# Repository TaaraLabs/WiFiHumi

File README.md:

Wifi Humidity Sensor
====================

[WebSite](https://taaralabs.eu/wh1)

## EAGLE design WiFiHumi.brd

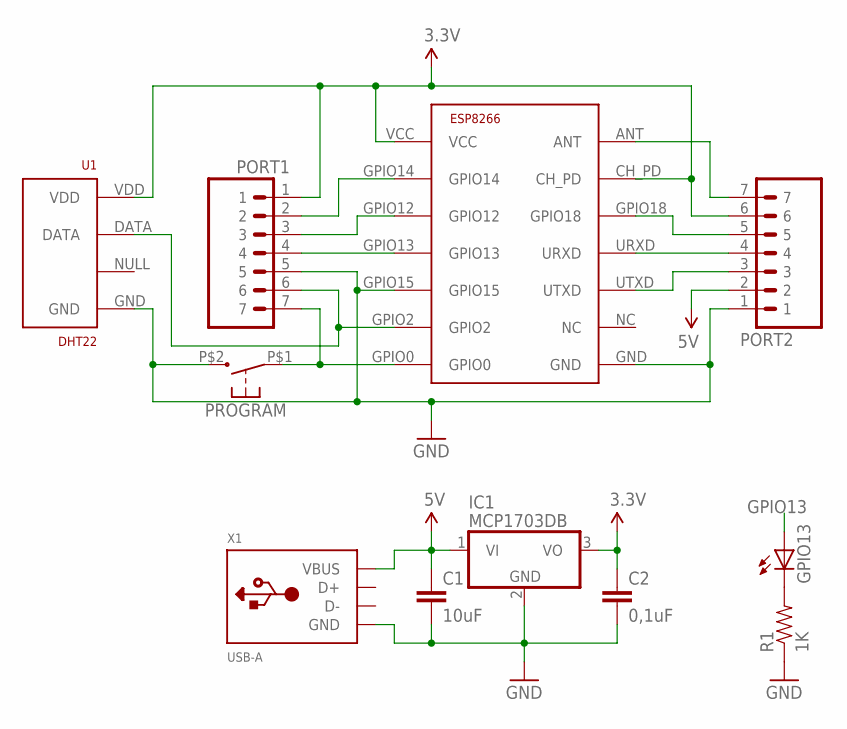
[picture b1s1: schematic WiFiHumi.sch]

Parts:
C1: 10uF; 0603-CAP
C2: 0,1uF; 0603-CAP
GPIO13: LEDCHIPLED_0603; CHIPLED_0603
IC1: MCP1703DB; SOT223
PORT1, PORT2: DIPLOCK7-FEMALE; 1X07_FEMALE_LOCK.010
PROGRAM: OMRON_B3U-1000_TACT_SW; BC3-1000
R1: 1K; 0603-RES
U1: DHT22; RHT03_DHT-22/RA
U$1: ESP8266; ESP-03
X1: USB-A; MOLEX_480371000

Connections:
3.3V: C2.1, IC1.3 (VO), PORT1.1, PORT2.6, U1.VDD, U$1.CH_PD, U$1.VCC
5V: C1.1, IC1.1 (VI), PORT2.2, X1.1 (VBUS)
ANT: PORT2.7, U$1.ANT
GND: C1.2, C2.2, IC1.2 (GND), PORT1.5, PORT2.1, PROGRAM.P$2 (3), R1.1, U1.GND, U$1.GND, U$1.GPIO15, X1.4 (GND)
GPIO0: PORT1.7, PROGRAM.P$1 (1), U$1.GPIO0
GPIO02: PORT1.6, U1.DATA, U$1.GPIO2
GPIO12: PORT1.3, U$1.GPIO12
GPIO13: GPIO13.A, PORT1.4, U$1.GPIO13
GPIO14: PORT1.2, U$1.GPIO14
GPIO18: PORT2.5, U$1.GPIO18
unnamed: GPIO13.C, R1.2
RXD: PORT2.4, U$1.URXD
TXD: PORT2.3, U$1.UTXD

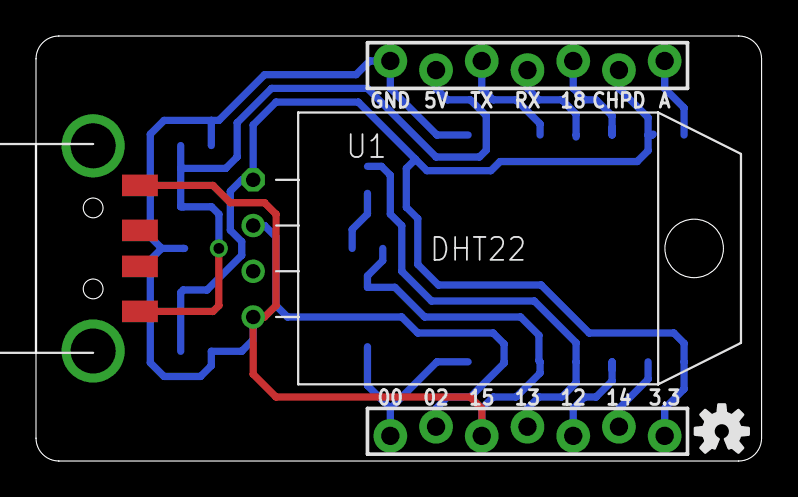
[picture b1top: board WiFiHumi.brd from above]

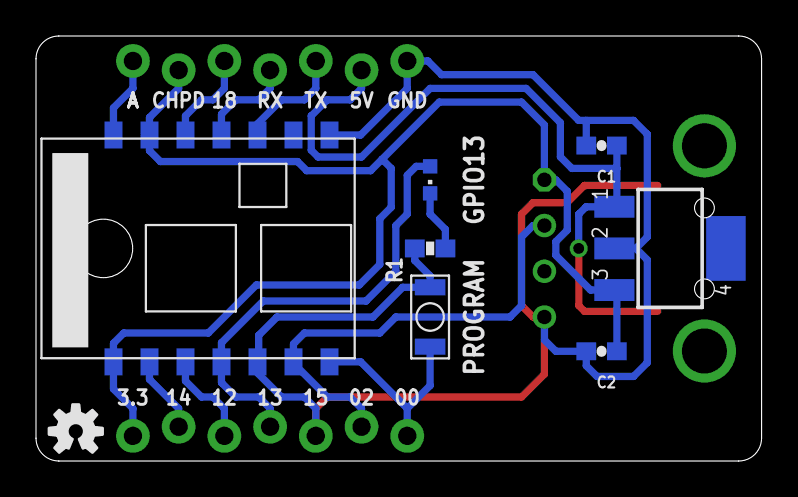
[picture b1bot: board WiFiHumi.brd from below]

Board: 2 copper layers, 40.3 x 23.6 mm, 13 parts (8 on the bottom side), 13 nets.

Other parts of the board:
U$4, U$5: OSHW-LOGO-S

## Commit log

2015-01-24 :neckbeard: Added .gitattributes & .gitignore files
2015-01-24 WifiHumi
2015-06-21 PCB Picture added

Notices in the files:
parts and their libraries:
SparkFun: Licensing: CC v3.0 Share-Alike You are welcome to use this library for commercial purposes.
